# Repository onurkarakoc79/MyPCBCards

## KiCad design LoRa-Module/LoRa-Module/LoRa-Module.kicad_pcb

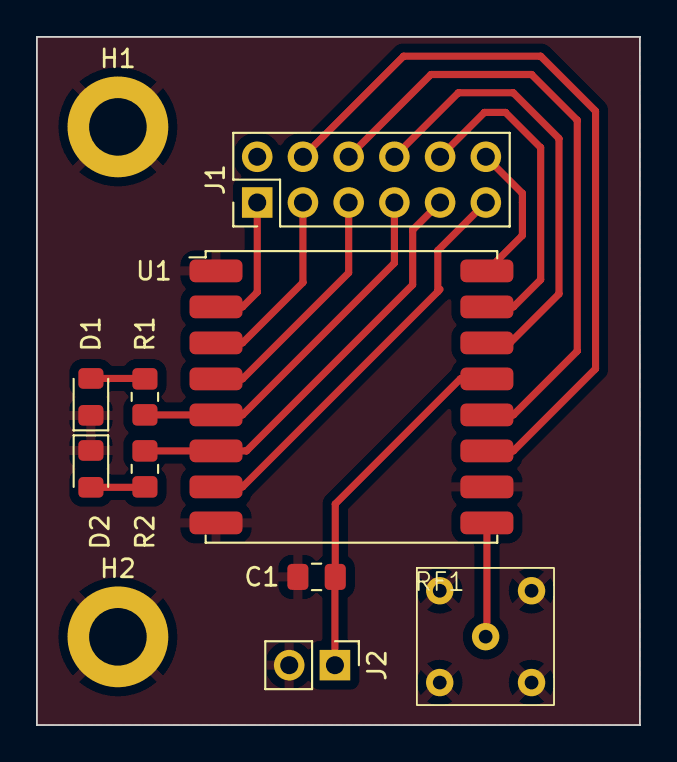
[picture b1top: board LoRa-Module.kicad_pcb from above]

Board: 2 copper layers, 33.5 x 38.2 mm, 11 parts (0 on the bottom side), 16 nets.

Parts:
C1: 10uF; C_0805_2012Metric_Pad1.18x1.45mm_HandSolder
D1, D2: LED; LED_0805_2012Metric_Pad1.15x1.40mm_HandSolder
H1, H2: MountingHole_Pad; MountingHole_3.2mm_M3_DIN965_Pad
J1: Conn_02x06_Counter_Clockwise; PinHeader_2x06_P2.54mm_Vertical
J2: Conn_01x02_Pin; PinHeader_1x02_P2.54mm_Vertical
R1, R2: 10kΩ 0402 50V; R_0805_2012Metric_Pad1.20x1.40mm_HandSolder
RF1: 5-1814832-2; LoRa-Antenn-Conn
U1: RFM95W-868S2; HOPERF_RFM9XW_SMD

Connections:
+3V3: C1.2, J2.1, U1.13 (3.3V)
/LORA_CS: J1.7, R1.2, U1.5 (NSS)
/LORA_DIO0: J1.8, U1.14 (DIO0)
/LORA_DIO1: J1.10, U1.15 (DIO1)
/LORA_DIO2: J1.12, U1.16 (DIO2)
/LORA_DIO3: J1.4, U1.11 (DIO3)
/LORA_DIO4: J1.6, U1.12 (DIO4)
/LORA_DIO5: J1.11, U1.7 (DIO5)
/LORA_MISO: J1.1, U1.2 (MISO)
/LORA_MOSI: J1.3, U1.3 (MOSI)
/LORA_RESET: J1.9, R2.2, U1.6 (RESET)
/LORA_SCK: J1.5, U1.4 (SCK)
GND: C1.1, D1.1 (K), D2.1 (K), H1.1, H2.1, J2.2, RF1.1, RF1.2, RF1.3, RF1.4, U1.1 (GND), U1.8 (GND), U1.10 (GND)
unnamed: D1.2 (A), R1.1
unnamed: D2.2 (A), R2.1
unnamed: RF1.5, U1.9 (ANT)

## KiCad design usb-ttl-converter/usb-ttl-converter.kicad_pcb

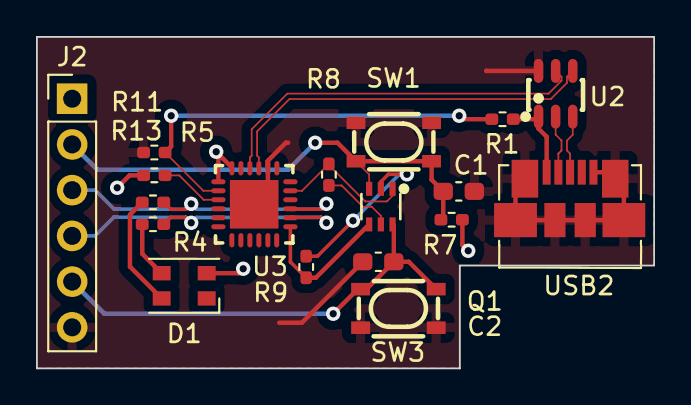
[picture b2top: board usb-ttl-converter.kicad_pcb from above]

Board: 2 copper layers, 34.3 x 18.4 mm, 18 parts (0 on the bottom side), 19 nets.

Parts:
C1, C2: 0.1uF; C_0603_1608Metric_Pad1.08x0.95mm_HandSolder
D1: LED_RKGB; LED_Cree-PLCC4_3.2x2.8mm_CCW
J2: Conn_01x06_Pin; PinHeader_1x06_P2.54mm_Vertical
Q1: SMBT3904DW1T1G; SOT-363_L2.0-W1.3-P0.65-LS2.1-BL
R1: 22.1k; R_0402_1005Metric_Pad0.72x0.64mm_HandSolder
R4, R5, R7, R8, R9: 10K; R_0402_1005Metric_Pad0.72x0.64mm_HandSolder
R11: 47.5k; R_0402_1005Metric_Pad0.72x0.64mm_HandSolder
R13: 1K; R_0402_1005Metric_Pad0.72x0.64mm_HandSolder
SW1, SW3: SKRPABE010; KEY-SMD_4P-L4.2-W3.2-P2.20-LS4.6
U2: STF202-22T1G; TSOP-6_L3.0-W1.5-P0.95-LS2.8-BL
U3: CP2102N-A02-GQFN24R; QFN-24_L4.0-W4.0-P0.50-TL-EP2.6
USB2: 47346-0001; MICRO-USB-SMD_47346-0001

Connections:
+3V3: D1.2 (K), J2.1, R7.1, R13.1, U3.6 (VDD), U3.7 (VREGIN)
/D+: U2.3 (D(IN)), USB2.3 (Data+)
/D-: U2.2 (D(IN)), USB2.2 (Data-)
/DCP+: U2.4 (D(OUT)), U3.3 (D+)
/DCP-: U2.5 (D(OUT)), U3.4 (D-)
BOOT: C1.1, J2.2, Q1.3 (C1), R7.2, SW1.1, SW1.2
DTR: Q1.1 (E2), R8.1, U3.23 (DTR)
EN: C2.1, J2.5, Q1.6 (C2), SW3.1, SW3.2
GND: C1.2, C2.2, J2.6, R11.1, SW1.3, SW1.4, SW3.3, SW3.4, U2.6 (GND), U3.2 (GND), U3.25 (GND), USB2.5 (GND), USB2.6
unnamed: D1.4 (BA), R4.1
unnamed: D1.3 (GA), R5.1
unnamed: Q1.5 (B1), R8.2
unnamed: Q1.2 (B2), R9.1
unnamed: R13.2, U3.9 (RSTb)
unnamed: R1.2, R11.2, U3.8 (VBUS)
RTS: Q1.4 (E1), R9.2, U3.19 (RTS)
RX+: J2.3, R4.2, U3.21 (TXD)
RX-: J2.4, R5.2, U3.20 (RXD)
VBUS: R1.1, U2.1 (VBUS), USB2.1 (VBUS)
